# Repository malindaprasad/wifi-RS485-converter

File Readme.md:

## Simple RS485 to WiFi Converter. 

This include ESP8266 WiFi Module, RS485 TTL Converter and 220V to 5V HiLink power supply. so simply can plug to main power

හුග දෙනෙක් Offgrid සොලර් ගහන නිසා  කලින් කරපු මේ PCB එක ශෙයා කරන්න හිතුන. පරිපථ හැදුවට මම PCB අදින්න වැඩිය දන්නෙ නැ. මිතුරකුගෙ සහයෙන් ඇදල JL PCB එකෙන් හදවල ගෙනාව. දැනට වසර කීපයක් ගැටලුවක් නැතිව Hybrid Inverter හා Easton SDM 120, SDM230 එක්ක ගැටලුවක් නැතිව ඩිවයිස් කීපයක් වැඩ. මෙයා කරන්නෙ ModBus එකෙන් දත්ත ටික අරන මගෙ සර්වරයකට යවන එක.  හුග දෙනෙක් වයර් අමුනල කරල අන්තිමට පිලිවෙලක් කරගන්න හිතන නිසයි මේක දැම්මෙ 

කෙලින්ම 5V එකකට දෙනවනම් HiLink එක ඔ්නෙ නැ. 
Inverter හරි ඩිවයිස් එකේ RS485 to TCP Converter එකක් එනවනම්, RS485 TTL එක නැතිව WiFi වලින් ඇදල ගන්නත් පුලුවන්. මම ඒ විදිහට එක ඩිවයිස් එකක් ගන්නව

කාට හරි ප්‍රයෝජනයක් වෙයි. වෙනස් කලොත්.. ගැටලුවක් හැදුවොත් මටත් කියන්න

zip එක කෙලින්ම දෙන්න පුලුවන් Printing සයිට් එකට 

### PCB 

### Schematic 

### Printed PCB

### Screens using data

Support by
@danindudesilva

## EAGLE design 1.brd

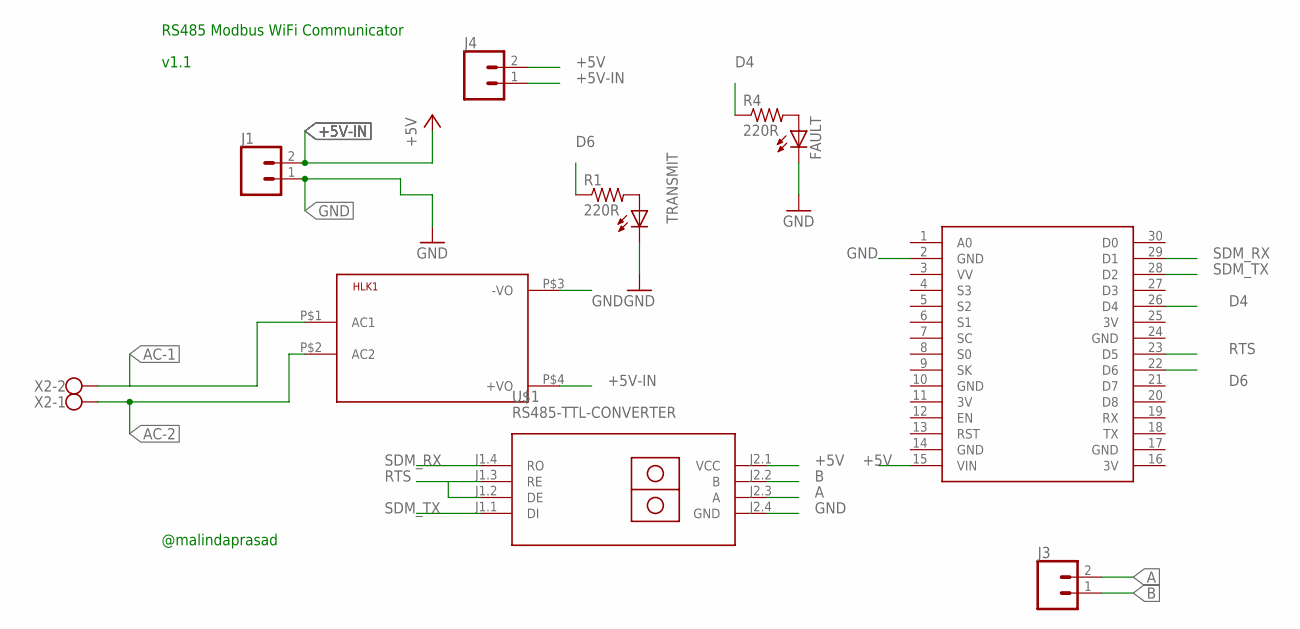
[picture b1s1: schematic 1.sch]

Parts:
FAULT: LED5MM
HLK1: HLK-PM013W; HLK-PM01
J1, J3, J4: CONN_02; 1X02
R1, R4: 220R; 0207/10
TRANSMIT: LED5MM
U$1: RS485-TTL-CONVERTER
U$2: NODEMCU
X2: W237-102

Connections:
3V: U$2.11 (3V), U$2.16 (3V), U$2.25 (3V)
+5V: J4.2, U$1.J2.1 (VCC), U$2.15 (VIN)
+5V-IN: HLK1.P$4 (+VO), J1.2, J4.1
A: J3.2, U$1.J2.3 (A)
AC-1: HLK1.P$1 (AC1), X2.2
AC-2: HLK1.P$2 (AC2), X2.1
B: J3.1, U$1.J2.2 (B)
D4: R4.1, U$2.26 (D4)
D6: R1.1, U$2.22 (D6)
GND: FAULT.K (C), HLK1.P$3 (-VO), J1.1, TRANSMIT.K (C), U$1.J2.4 (GND), U$2.2 (GND), U$2.10 (GND), U$2.14 (GND), U$2.17 (GND), U$2.24 (GND)
unnamed: R1.2, TRANSMIT.A
unnamed: FAULT.A, R4.2
RTS: U$1.J1.2 (DE), U$1.J1.3 (RE), U$2.23 (D5)
SDM_RX: U$1.J1.4 (RO), U$2.29 (D1)
SDM_TX: U$1.J1.1 (DI), U$2.28 (D2)

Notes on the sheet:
@malindaprasad
v1.1
RS485 Modbus WiFi Communicator

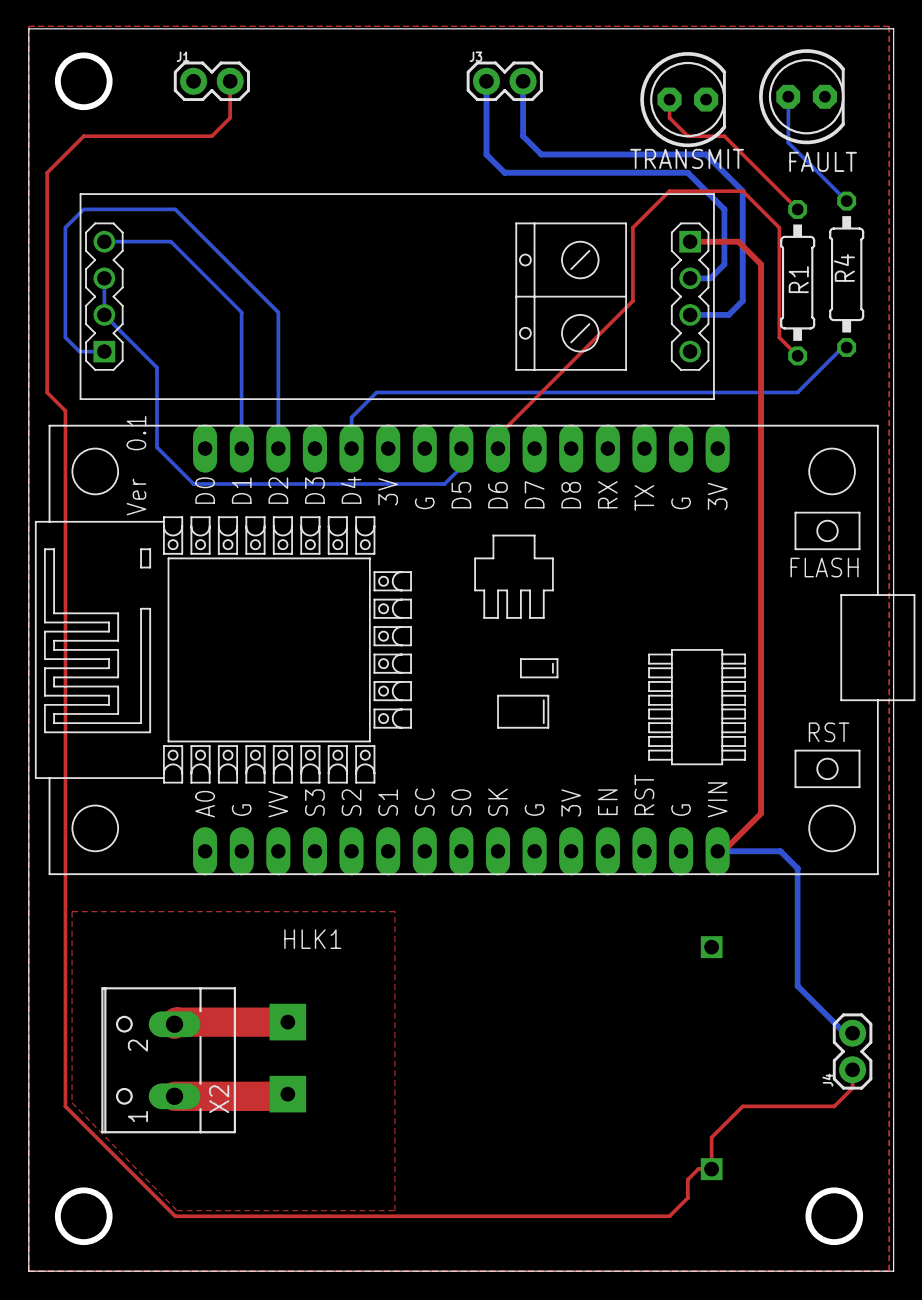
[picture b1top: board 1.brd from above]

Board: 2 copper layers, 59.6 x 85.8 mm, 11 parts (0 on the bottom side), 15 nets.

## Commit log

2022-01-09 added Photo

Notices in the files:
parts and their libraries:
diy-modules: Released under the Creative Commons Attribution 4.0 International License: http://creativecommons.org/licenses/by/4.0
SparkFun-Connectors: Licensing: Creative Commons ShareAlike 4.0 International - https://creativecommons.org/licenses/by-sa/4.0
